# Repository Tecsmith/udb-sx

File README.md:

# Unified Daughterboard SX

> Based on https://github.com/Unified-Daughterboard/UDB-S  
> &copy; 2023 Unified Daughterboard Project

The Unified Daughterboard is an open standard to unify the USB daughterboards used in custom mechanical keyboard projects.

## This spinoff 

The UDB project has progressed to 3 distinct variants:
- C-JSH with JST PH connector
- C-EZM with Molex Pico-EZmate connector
- and a thinner variant S, also with EZmate connector

These new C5 and S1 variants have opted to merge shield grounding and cable ground, but this variant of the S is, *a)* more cautious on case/cable grounding and protects the circuit ground with a 4.7 µF capacitor and a 1 MΩ resistor that are used as a **common EMI (Electromagnetic Interference) and ESD (Electrostatic Discharge) filtering network**, and *b)* uses the JST connector of the original C3 project.

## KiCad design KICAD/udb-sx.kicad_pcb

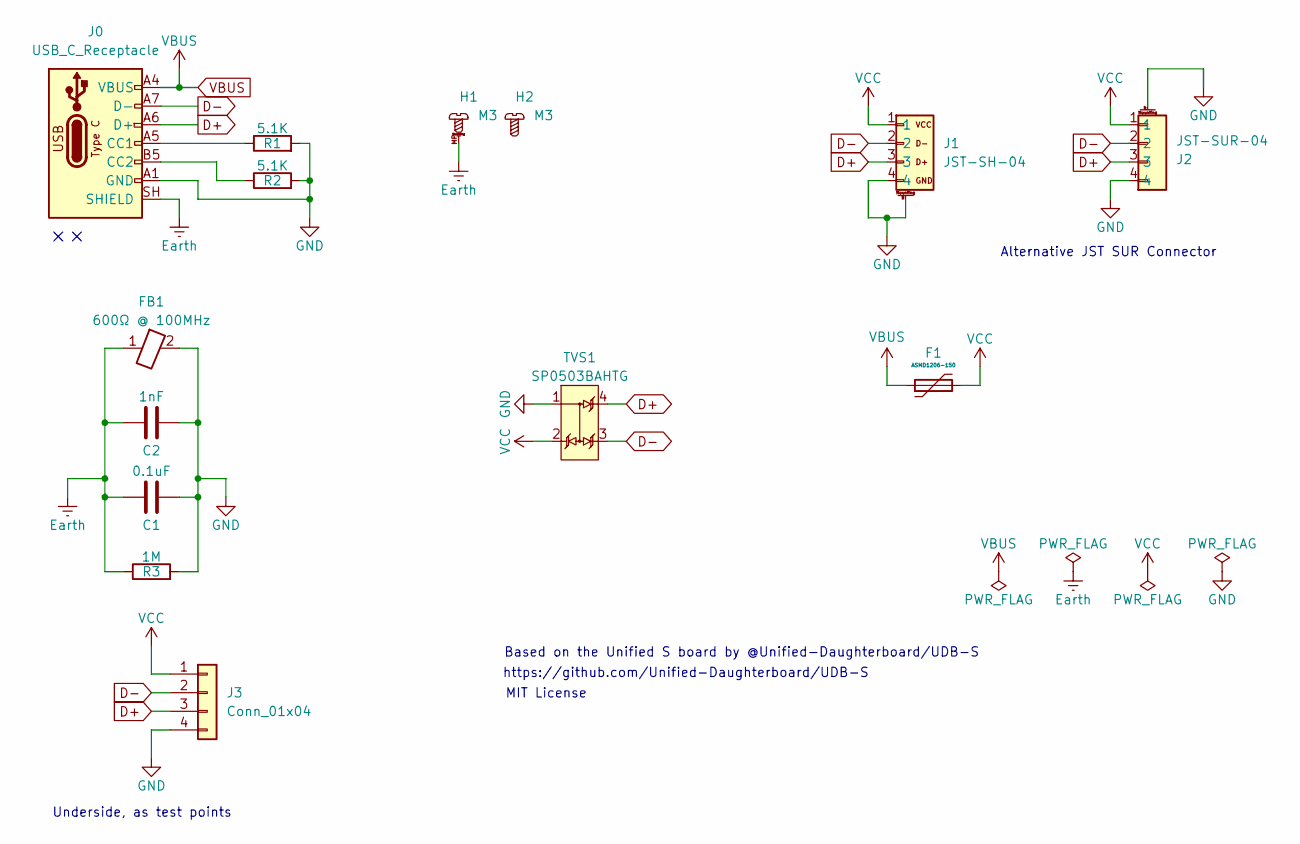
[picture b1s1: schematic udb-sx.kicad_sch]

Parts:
C1: 0.1uF; C_0603_1608Metric
C2: 1nF; C_0603_1608Metric
F1: ASMD1206-150; Fuse_1206_3216Metric; Manufacturer Part No ASMD1206-150; LCSC Part No C135342
FB1: 600Ω @ 100MHz; L_0603_1608Metric
H1: M3; MountingHole_3.2mm_M3_Pad_Via
H2: M3
J0: USB_C_Receptacle; USB_C_Receptacle_HRO_TYPE-C-31-M-12
J1: JST-SH-04; JST_SH_SM04B-SRSS-TB_1x04-1MP_P1.00mm_Horizontal
J2: JST-SUR-04; JST_SUR_SM04B-SURS-TF_1x04-1MP_P0.80mm_Horizontal
J3: Conn_01x04; 1x04_P2.54mm_SolderPads
R1, R2: 5.1K; R_0603_1608Metric
R3: 1M; R_0603_1608Metric
TVS1: SP0503BAHTG; SOT-143

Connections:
D+: J0.A6 (D+), J0.B6 (D+), J1.3, J2.3, J3.3, TVS1.4 (C4)
D-: J0.A7 (D-), J0.B7 (D-), J1.2, J2.2, J3.2, TVS1.3 (C3)
Earth: C1.1, C2.1, FB1.1, H1.MP, J0.SH (SHIELD), R3.1
GND: C1.2, C2.2, FB1.2, J0.A1 (GND), J0.A12 (GND), J0.B1 (GND), J0.B12 (GND), J1.4, J1.MP, J2.4, J2.MP, J3.4, R1.2, R2.2, R3.2, TVS1.1 (A)
unnamed: J0.A5 (CC1), R1.1
unnamed: J0.B5 (CC2), R2.1
VBUS: F1.1, J0.A4 (VBUS), J0.A9 (VBUS), J0.B4 (VBUS), J0.B9 (VBUS)
VCC: F1.2, J1.1, J2.1, J3.1, TVS1.2 (C2)

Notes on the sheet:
MIT License
Alternative JST SUR Connector
Underside, as test points
Based on the Unified S board by @Unified-Daughterboard/UDB-S
https://github.com/Unified-Daughterboard/UDB-S

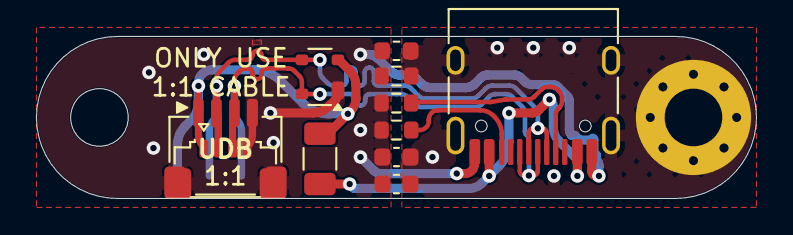
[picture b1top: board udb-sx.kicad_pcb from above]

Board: 2 copper layers, 40.0 x 9.0 mm, 13 parts (1 on the bottom side), 8 nets.

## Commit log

2025-12-29 init
